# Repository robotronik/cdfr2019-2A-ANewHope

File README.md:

# Robot 2A Martine - A New Hope

## Contexte et objectifs:
La carte de la base roulante et celle de l'ascenseur initialement prévues ne pourront pas etre prêtes dans les temps. Après discusion avec l'équipe du robot 1A, il n'y a que peu de choses sur lesquelles preter main forte. Il serait donc possible de continuer à travailler sur le robot 2A pour pouvoir présenter une version minimale de celui-ci à la coupe.

L'objectif serait de passer l'homologation et de pouvoir pousser quelques palets au cours de la coupe. Pour espérer être dans les temps, il est vital de faire au plus simple afin de disposer d'une base méca/elec prete, avec le code haut niveau à faire sur la route.

La version B du robot abandonne l'ascenseur pour ne garder qu'un étage base roulante + un étage contrôle. D'un point de vue mécanique: la base roulante est quasiment prête et l'étage de controle peut être assemblé rapidement.

Volontaires:
* Victor (Mécanique, Elec)
* Félix (Elec)
* Raphael (Elec: Carte alimentation & Code)
* Arnaud (Elec: carte ultrason)

Conseil:
* Iris (Mécanique)

A confirmer:
* Vincent (Elec et prog?)

## Nouvelle structure:
Après discution avec Felix, Iris et Luc: idéalement, il aurait fallu récupérer la carte de la base roulante de l'année dernière, mais le STM32 dessus étant mort, et des levels shifters devant etre implémentés, faire rapidement une nouvelle carte est plus simple. La nouvelle structure serait donc la suivante (en gras: les cartes électroniques):

* Etage de contrôle:
  * **Carte de controle (CC)**:
    * [STM32 Nucleo-64 F401RE](https://www.st.com/en/evaluation-tools/nucleo-f401re.html)
  * **Carte d'alimentation**
  * Batterie
* Etage base roulante (Méca finie)
  * Moteurs (En place)
  * [Ecodeurs UsDigital S4T](https://www.usdigital.com/products/encoders/incremental/rotary/shaft/S4T?specification=mechanical#description) (En place)
  * Capteurs ultrasons (ref à définir)
  * **Carte adaptateur nappe moteur-pin** (car réutilisable facilement si à part)
  * **Carte de controle base roulante (CBR)**:
    * [Nucleo-32 F303K8](https://www.st.com/en/evaluation-tools/nucleo-f303k8.html) de format Arduino Nano, programmable avec l'IDE Arduino
    * Level shifters pour communiquer avec les encodeurs ([par exemple ceux-ci](https://www.sparkfun.com/products/12009))
    * Driver moteurs: à commander et si possible à integrer directement sur la carte
  * **Carte capteur ultrasons (CU)**

## Avancement:

Tâches de la partie méca (Victor):
* Impression des dernieres équerres
* Assemblage de l'étage de controle
* Découpe au fablab des parois/bases plexiglass
* Design et impression (ou adaptation) de supports pour les cartes électroniques

Tâches de la partie électronique:
* Carte alimentation à finir (Raph')
* Carte base roulante à faire (Victor & Félix)
* Carte nappe moteur-pin à vérifier et imprimer
* Carte ultrason à faire (Arnaud)

Tâches de de partie Code:
* Finir l'asservissement PID (nécessite la base roulante prete) (Raph')

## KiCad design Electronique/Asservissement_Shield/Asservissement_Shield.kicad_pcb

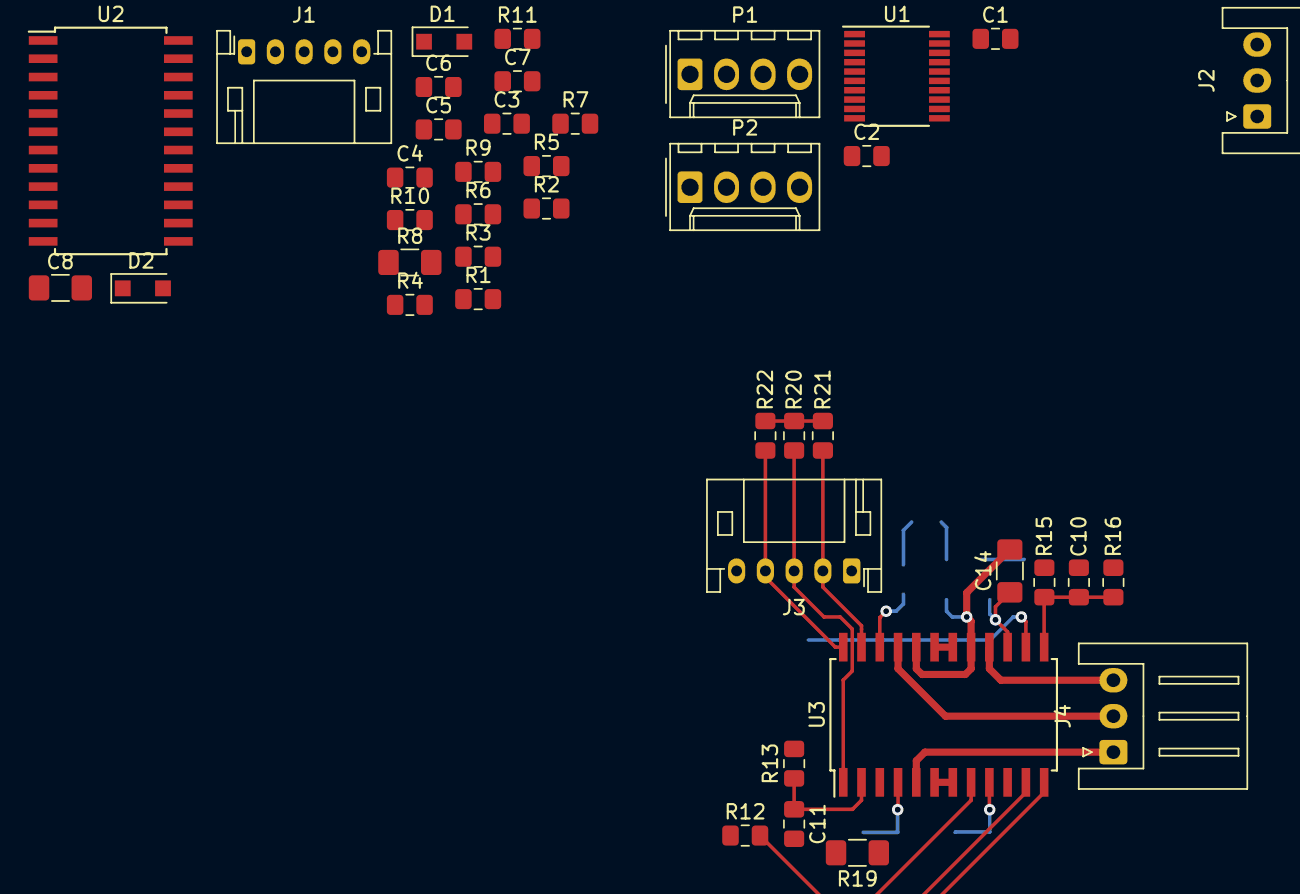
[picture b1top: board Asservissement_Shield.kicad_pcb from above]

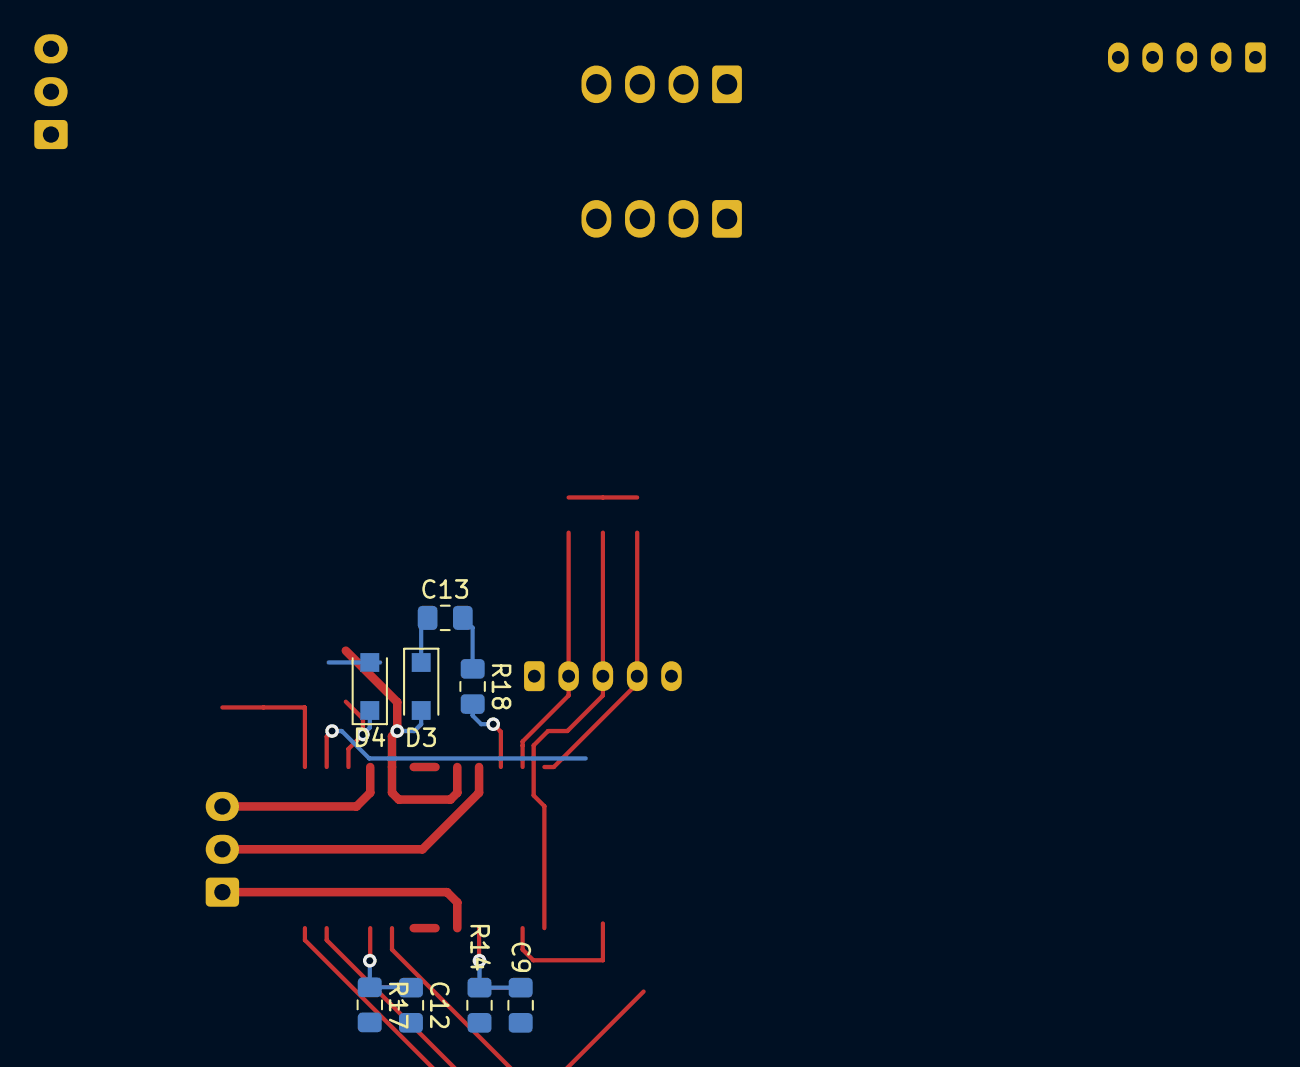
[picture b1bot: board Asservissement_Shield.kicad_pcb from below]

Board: 2 copper layers, 49 parts (8 on the bottom side), 40 nets.

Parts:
C1, C2: 100n; C_0805_2012Metric_Pad1.15x1.40mm_HandSolder
C3, C6, C9, C12: 1n; C_0805_2012Metric_Pad1.15x1.40mm_HandSolder
C4, C7, C10, C13: 10n; C_0805_2012Metric_Pad1.15x1.40mm_HandSolder
C5, C11: 5.6n; C_0805_2012Metric_Pad1.15x1.40mm_HandSolder
C8, C14: 220n; C_1206_3216Metric_Pad1.42x1.75mm_HandSolder
D1, D2, D3, D4: 1N4148; D_SOD-123F
J1, J3: Hall_Sensor; JST_PH_S5B-PH-K_1x05_P2.00mm_Horizontal
J2, J4: Windings; JST_XH_S3B-XH-A_1x03_P2.50mm_Horizontal
P1, P2: encoder_2; Molex_KK-254_AE-6410-04A_1x04_P2.54mm_Vertical
R1, R12: 1k; R_0805_2012Metric_Pad1.15x1.40mm_HandSolder
R2, R13: 100k; R_0805_2012Metric_Pad1.15x1.40mm_HandSolder
R3, R14: 35k; R_0805_2012Metric_Pad1.15x1.40mm_HandSolder
R4, R15: 1k2; R_0805_2012Metric_Pad1.15x1.40mm_HandSolder
R5, R16: 220; R_0805_2012Metric_Pad1.15x1.40mm_HandSolder
R6, R17: 47k; R_0805_2012Metric_Pad1.15x1.40mm_HandSolder
R7, R18: 100; R_0805_2012Metric_Pad1.15x1.40mm_HandSolder
R8, R19: 0.3; R_1206_3216Metric_Pad1.42x1.75mm_HandSolder
R9, R10, R11, R20, R21, R22: 0; R_0805_2012Metric_Pad1.15x1.40mm_HandSolder
U1: TXS0108EPW; TSSOP-20_4.4x6.5mm_P0.65mm
U2, U3: L6235PD; SOIC-24W_7.5x15.4mm_P1.27mm

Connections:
+3V3: C1.1, R1.1, R4.1, R12.1, R15.1, U1.2, U1.10
+5V: C2.1, P1.1, P2.1, R9.1, R10.1, R11.1, R20.1, R21.1, R22.1, U1.19
/Diagnostic_1: C11.1, R13.1, U3.2, U3.12
/Diagnostic_2: C5.1, R2.1, U2.2, U2.12
/Encoders/Ch_A1(+5V): P1.2, U1.15
/Encoders/Ch_A2(+5V): P2.2, U1.13
/Encoders/Ch_B1(+5V): P1.4, U1.14
/Encoders/Ch_B2(+5V): P2.4, U1.12
/MotorA/Hall_Sensor1: J1.3, R9.2, U2.1
/MotorA/Hall_Sensor2: J1.2, R10.2, U2.23
/MotorA/Hall_Sensor3: J1.4, R11.2, U2.24
/MotorA/Motor_Winding1: J2.1, U2.5
/MotorA/Motor_Winding2: J2.2, U2.21
/MotorA/Motor_Winding3: J2.3, U2.16
/MotorB/Hall_Sensor1: J3.3, R20.2, U3.1
/MotorB/Hall_Sensor2: J3.2, R21.2, U3.23
/MotorB/Hall_Sensor3: J3.4, R22.2, U3.24
/MotorB/Motor_Winding1: J4.1, U3.5
/MotorB/Motor_Winding2: J4.2, U3.21
/MotorB/Motor_Winding3: J4.3, U3.16
/Tachometer_1: R12.2, U3.8
/Tachometer_2: R1.2, U2.8
GND: C1.2, C2.2, C3.2, C4.2, C5.2, C6.2, C9.2, C10.2, C11.2, C12.2, J1.1, J3.1, P1.3, P2.3, R3.2, R5.2, R6.2, R8.1, R14.2, R16.2, R17.2, R19.1, U1.11, U2.6, U2.7, U2.18, U2.19, U3.6, U3.7, U3.18, U3.19
unnamed: C3.1, R3.1, U2.4
unnamed: C4.1, R4.2, R5.1, U2.13
unnamed: C6.1, R6.1, U2.9
unnamed: C7.1, D1.1, D2.2
unnamed: C7.2, R7.1
unnamed: C8.1, D2.1, U2.15
unnamed: C9.1, R14.1, U3.4
unnamed: C10.1, R15.2, R16.1, U3.13
unnamed: C12.1, R17.1, U3.9
unnamed: C13.1, D3.1, D4.2
unnamed: C13.2, R18.1
unnamed: C14.1, D4.1, U3.15
unnamed: R7.2, U2.22
unnamed: R8.2, U2.3, U2.10
unnamed: R18.2, U3.22
unnamed: R19.2, U3.3, U3.10
VCC: C8.2, C14.2, D1.2, D3.2, U2.17, U2.20, U3.17, U3.20

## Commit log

2019-02-11 Add initial files
2019-02-11 Add initial files, working HAL
2019-03-08 Add eeprom code
2019-03-08 Code for encoders.
2019-03-08 reset encoders after setup
2019-03-15 adc ok ?
2019-03-15 cleanup
2019-04-10 code for print and encoders tested
2019-04-13 Moteurs
2019-04-13 FIX LE LINK DE SES MORTS ERROR VFP
2019-04-13 Test moteurs
2019-04-13 Fix header
2019-04-16 small makefile + main cleanups
2019-04-16 push code for motors
2019-04-17 test
2019-04-29 correct configuration and added make tsmr.debug with triggers gdb
2019-04-29 git ignore *.log
2019-04-29 reorganisation
2019-04-29 interruptions on timer 15
2019-04-30 motor control with PWM, pins are correct for motors.h
2019-04-30 good for basic tests
2019-04-30 Add tests target (make tests.flash). Add back some lowlevel sources in makefile.
2019-04-30 Add install_udev rule
2019-04-30 Fix debug. update test.
2019-05-01 Weird bug in libopencm3 ? or in stm32 ? Works with this code.
2019-05-01 disable warning
2019-05-01 Fix orientation
2019-05-01 Fix double / float Add tests
2019-05-01 Fix MACRO FUCKING PARENTHÈSES. Fix valeurs. Fix calcul (signe).
2019-05-01 Update Odometry code (add print, change to delta-theta asser)
2019-05-01 Limit motor currents
2019-05-01 "Final" main function, correct PID.
2019-05-03 rename, cleanup.
2019-05-03 Fix make clean function
2019-05-03 Add "calibration.{c,h}". Move asservissement files to asservissement dir.
2019-05-06 Ajout des infos pour l'organisation
2019-05-06 ajout dossier
2019-05-06 Add electronics (not finished)
2019-05-06 fix 5v / 3v3
2019-05-06 routage
2019-05-06 oops
2019-05-09 Add small board for encoder level shifting
2019-05-09 Ajout Test_ToF
    Jeu de test pour 1 ToF de la carte Ultraphotonic Sense
2019-05-09 Test_ToToF en callback
    Jeu de test d'1 servo en callback avec un seuil de détection
2019-05-10 Moved code to subdir
2019-05-10 asservissement board works fine
2019-05-10 add submodule
2019-05-13 Clean up
2019-05-13 Add submodules
2019-05-22 update submodule
2019-05-26 Final position code setup
